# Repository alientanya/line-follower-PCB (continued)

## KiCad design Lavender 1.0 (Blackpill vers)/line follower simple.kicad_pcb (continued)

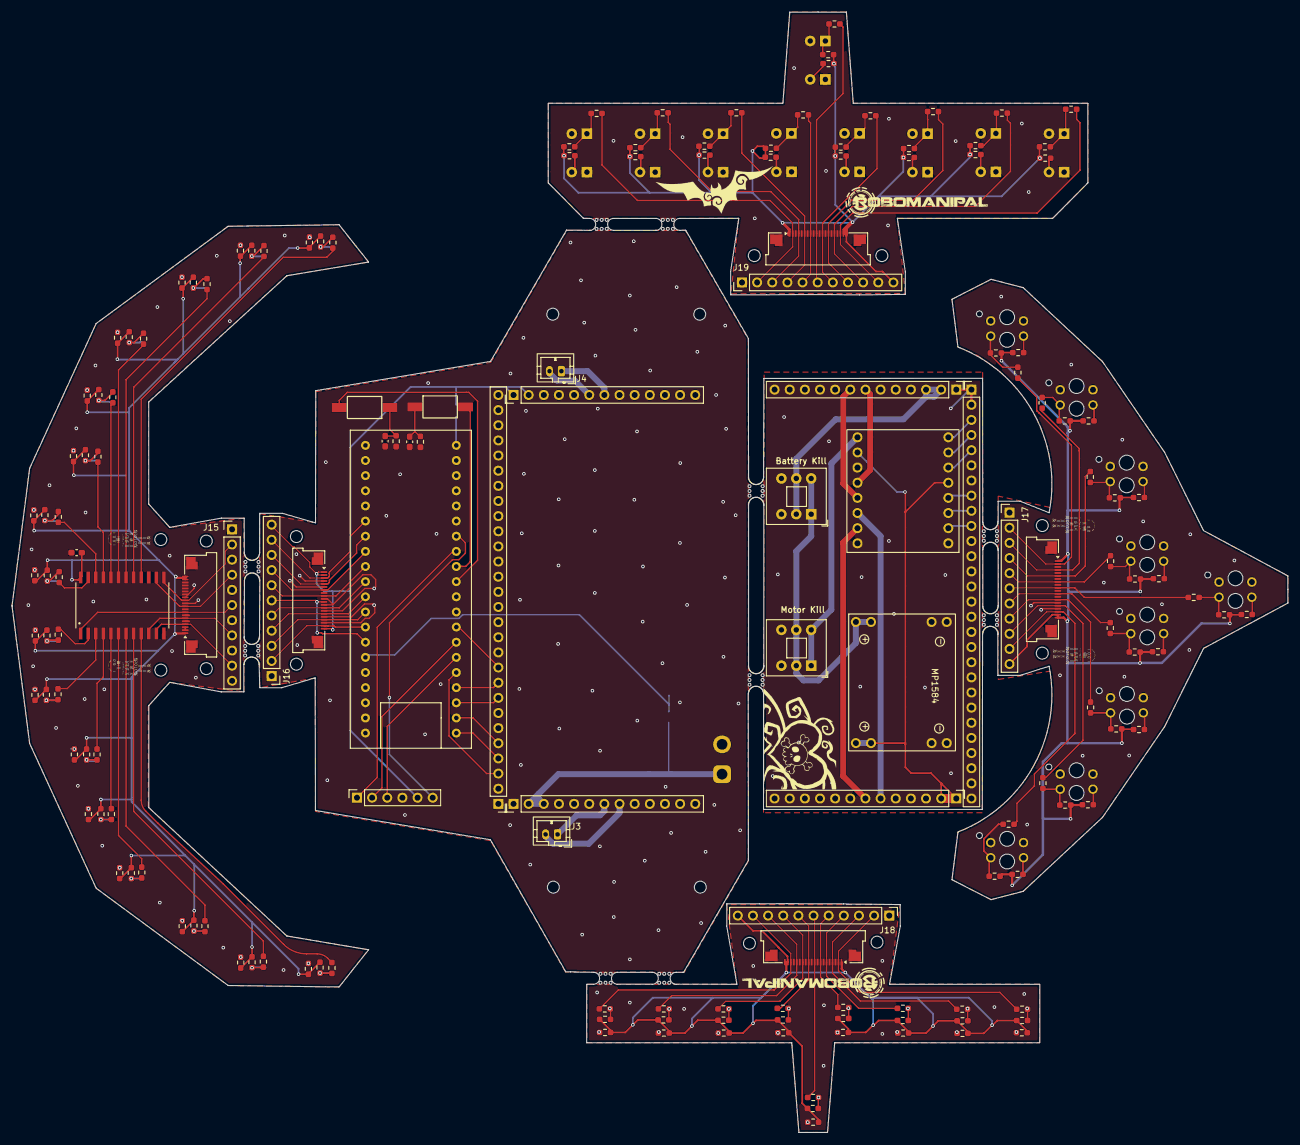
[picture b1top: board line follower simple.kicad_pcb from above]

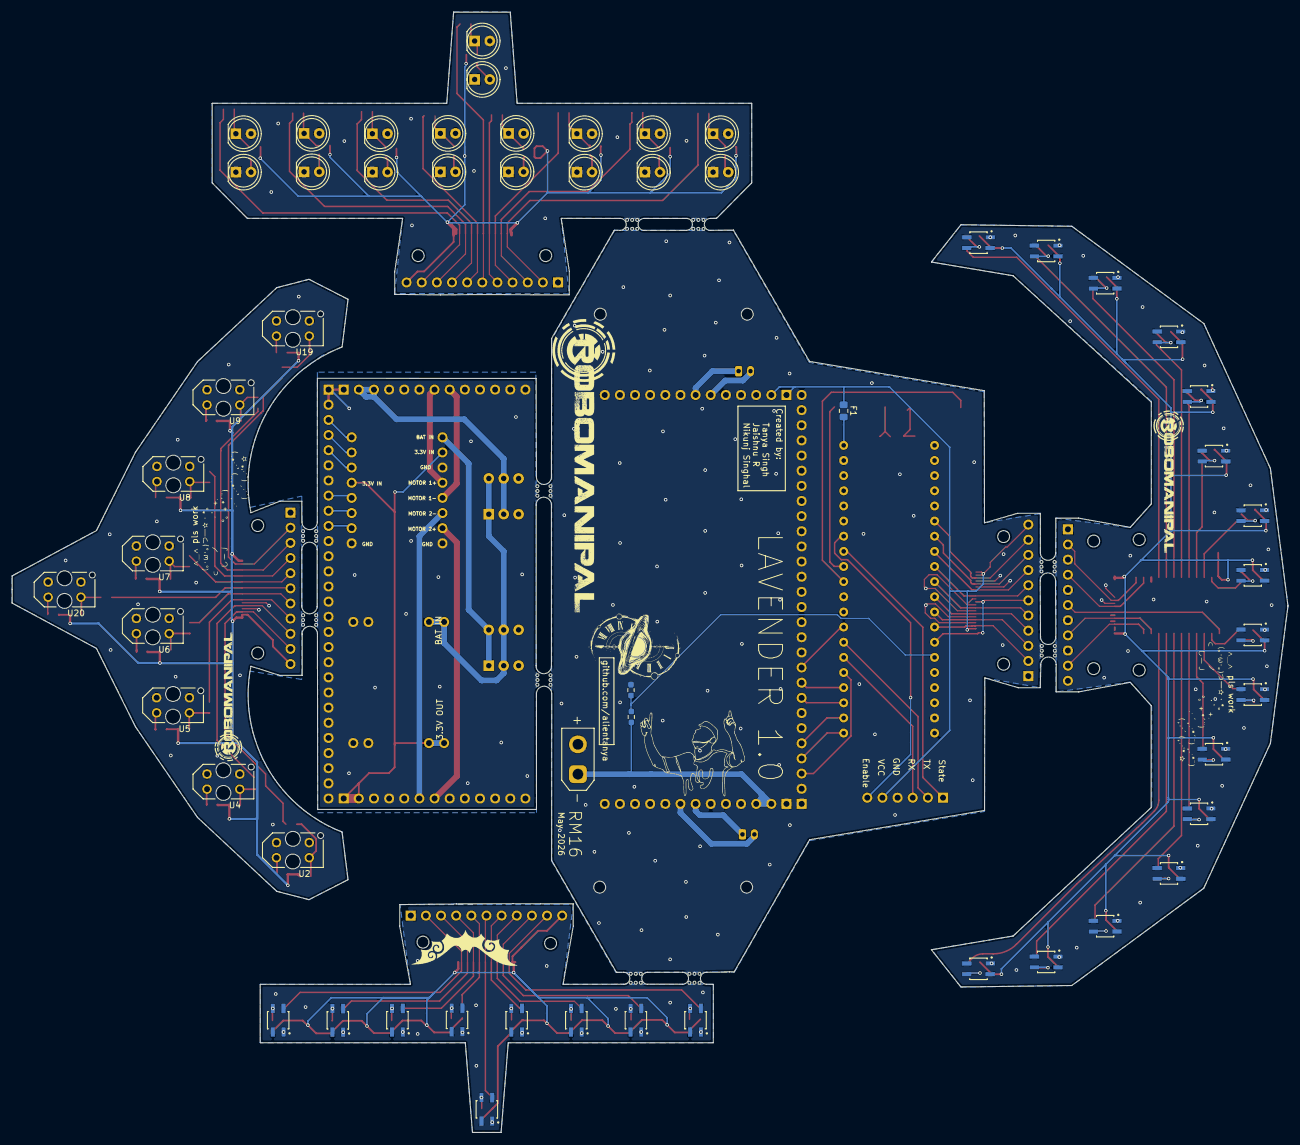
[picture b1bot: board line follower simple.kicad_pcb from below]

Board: 2 copper layers, 214.0 x 187.9 mm, 235 parts (56 on the bottom side), 179 nets.

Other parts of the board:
mouse-bite-2.54mm-slot, mouse-bite-2.54mm-slot#2, mouse-bite-2.54mm-slot#3, mouse-bite-2.54mm-slot#4, mouse-bite-2.54mm-slot#5, mouse-bite-2.54mm-slot#6: VAL**; mouse-bite-2.54mm-slot

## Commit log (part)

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2026-04-03 Updated schematic
2026-04-03 Added switches
2026-04-04 Completed schematic layout
2026-04-05 Fixed ERC error
2026-04-07 arrange pcb components
2026-04-11 started routing
2026-04-12 Finished 16 sensor array
2026-04-14 Start third sensor array
2026-04-15 Start custom sensor array
2026-04-16 Finished PCB
2026-04-23 Curved array for tcrt500
2026-04-26 add images
2026-04-30 Add mousebites
2026-04-30 Add JST for motor
2026-04-30 Add silkscreen
2026-04-30 fix placement
2026-04-30 Add name
2026-05-01 Add date
2026-05-08 minor fixes
2026-05-19 Add polyfuse
2026-05-19 Silkscreen fixes
2026-05-20 Fix overlapping silkscreen
2026-05-28 fix footprint
2026-06-01 final
2026-06-01 fix gitignore
2026-06-01 gap fixes
2026-06-01 more gap fixes
